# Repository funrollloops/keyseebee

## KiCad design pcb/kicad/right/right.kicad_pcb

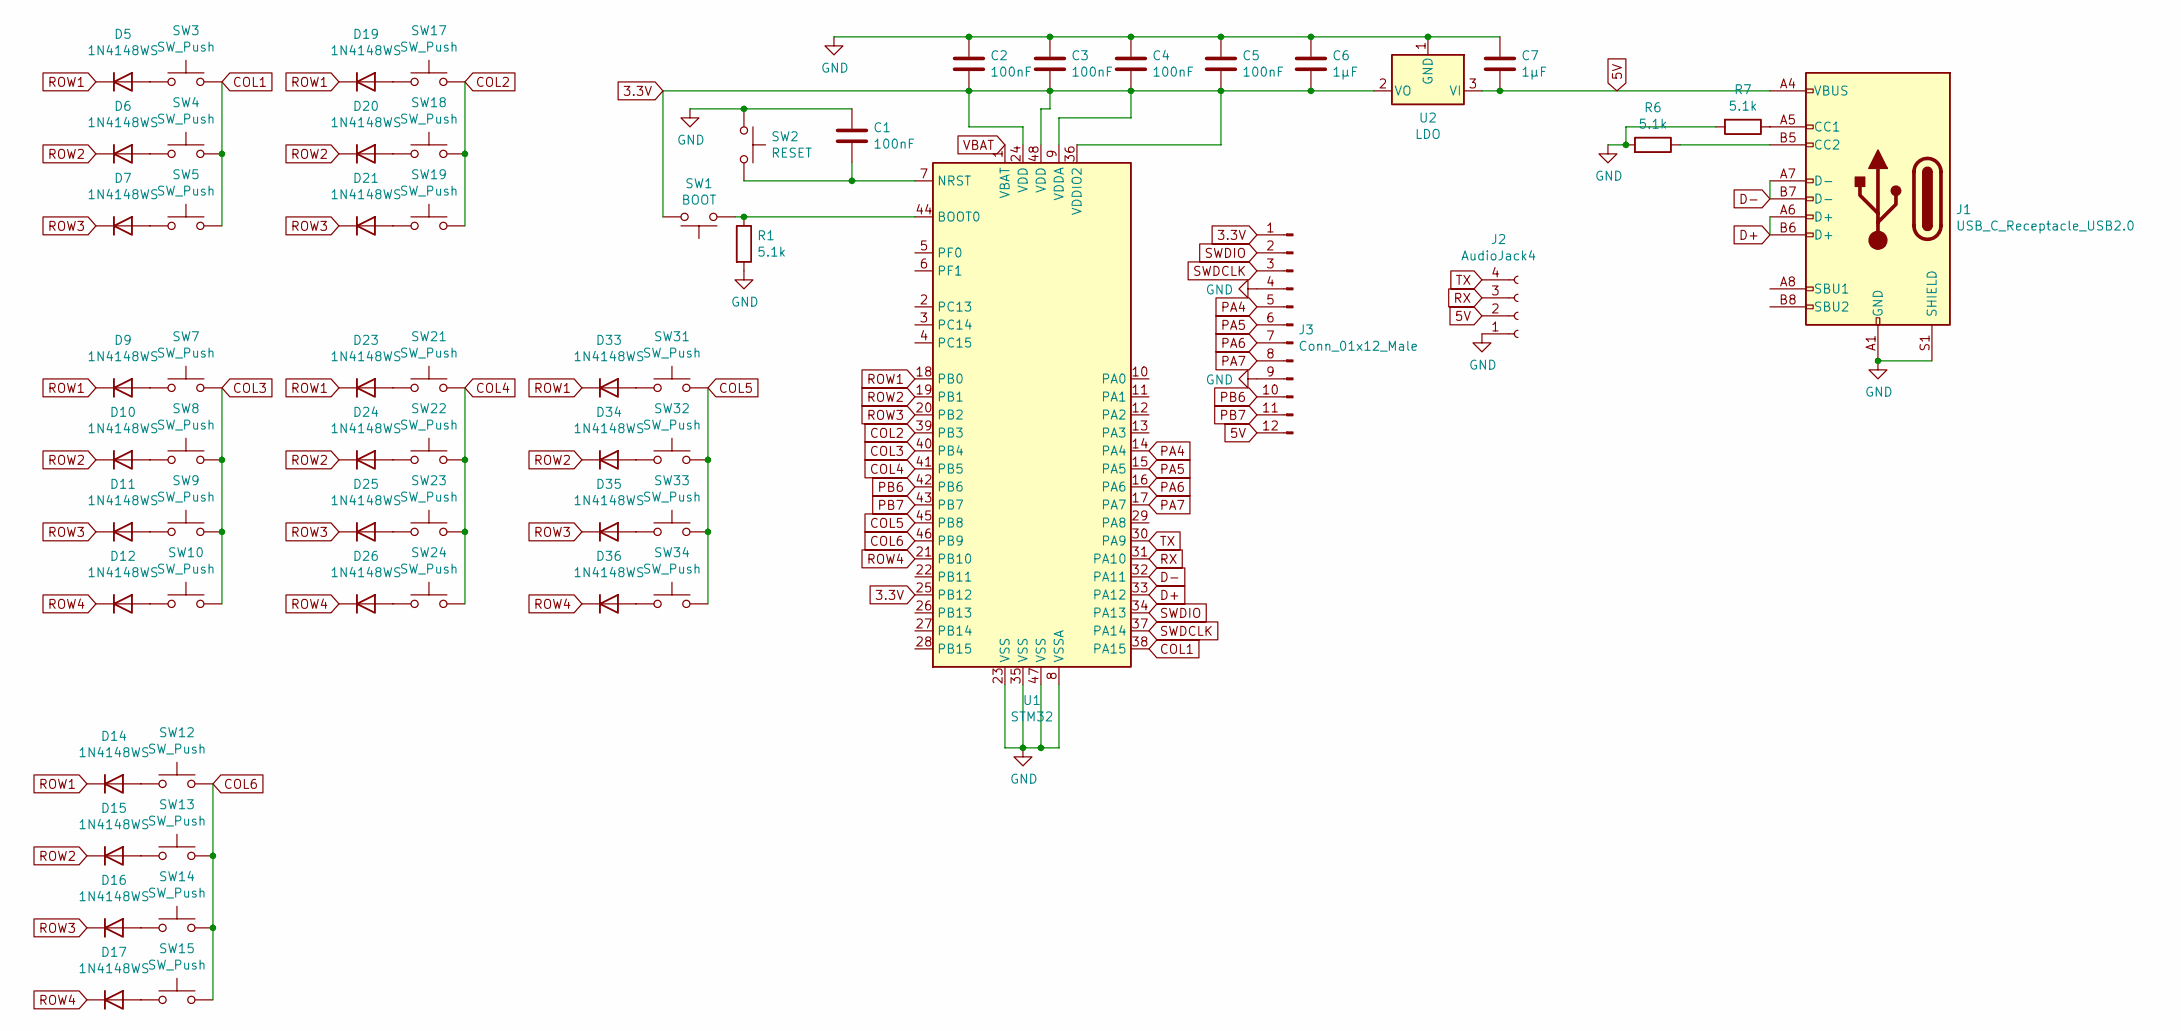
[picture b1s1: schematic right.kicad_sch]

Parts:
C1, C2, C3, C4, C5: 100nF; 0805; JLC C49678
C6, C7: 1µF; 0805; JLC C28323
D5, D6: 1N4148WS; SOD323; JLCPCB Part # C2128
D7, D9, D10, D11, D12, D14, D15, D16, D17, D19, D20, D21, D23, D24, D25, D26, D33, D34, D35, D36: 1N4148WS; SOD323; JLC C2128
J1: USB_C_Receptacle_USB2.0; USB_C_Receptacle_HRO_TYPE-C-31-M-12
J2: AudioJack4; TRRS-PJ-320A-no-Fmask
J3: Conn_01x12_Male; Harwin_M20-89012xx_1x12_P2.54mm_Horizontal
R1, R6, R7: 5.1k; 0805; JLC C27834
SW1: BOOT; SW_SPST_CK_RS282G05A3
SW2: RESET; SW_SPST_CK_RS282G05A3
SW3, SW4, SW5, SW7, SW8, SW9, SW10, SW12, SW13, SW14, SW15, SW17, SW18, SW19, SW21, SW22, SW23, SW24, SW31, SW32, SW33, SW34: SW_Push; CherryMX_Choc_1u
U1: STM32; LQFP-48_7x7mm_P0.5mm; JLCPCB Part # C8734
U2: LDO; SOT-23

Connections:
3.3V: C2.2, C3.2, C4.2, C5.2, C6.2, J3.1, SW1.2, U1.9 (VDDA), U1.24 (VDD), U1.25 (PB12), U1.36 (VDDIO2), U1.48 (VDD), U2.2 (VO)
5V: C7.2, J1.A4 (VBUS), J1.A9 (VBUS), J1.B4 (VBUS), J1.B9 (VBUS), J2.2, J3.12, U2.3 (VI)
COL1: SW3.2, SW4.2, SW5.2, U1.38 (PA15)
COL2: SW17.2, SW18.2, SW19.2, U1.39 (PB3)
COL3: SW7.2, SW8.2, SW9.2, SW10.2, U1.40 (PB4)
COL4: SW21.2, SW22.2, SW23.2, SW24.2, U1.41 (PB5)
COL5: SW31.2, SW32.2, SW33.2, SW34.2, U1.45 (PB8)
COL6: SW12.2, SW13.2, SW14.2, SW15.2, U1.46 (PB9)
D+: J1.A6 (D+), J1.B6 (D+), U1.33 (PA12)
D-: J1.A7 (D-), J1.B7 (D-), U1.32 (PA11)
GND: C1.1, C2.1, C3.1, C4.1, C5.1, C6.1, C7.1, J1.A1 (GND), J1.A12 (GND), J1.B1 (GND), J1.B12 (GND), J1.S1 (SHIELD), J2.1, J3.4, J3.9, R1.2, R6.2, R7.2, SW2.1, U1.8 (VSSA), U1.23 (VSS), U1.35 (VSS), U1.47 (VSS), U2.1 (GND)
unnamed: D5.2 (A), SW3.1
unnamed: D6.2 (A), SW4.1
unnamed: D7.2 (A), SW5.1
unnamed: D9.2 (A), SW7.1
unnamed: D10.2 (A), SW8.1
unnamed: D11.2 (A), SW9.1
unnamed: D12.2 (A), SW10.1
unnamed: D14.2 (A), SW12.1
unnamed: D15.2 (A), SW13.1
unnamed: D16.2 (A), SW14.1
unnamed: D17.2 (A), SW15.1
unnamed: D19.2 (A), SW17.1
unnamed: D20.2 (A), SW18.1
unnamed: D21.2 (A), SW19.1
unnamed: D23.2 (A), SW21.1
unnamed: D24.2 (A), SW22.1
unnamed: D25.2 (A), SW23.1
unnamed: D26.2 (A), SW24.1
unnamed: D33.2 (A), SW31.1
unnamed: D34.2 (A), SW32.1
unnamed: D35.2 (A), SW33.1
unnamed: D36.2 (A), SW34.1
unnamed: J1.A5 (CC1), R7.1
unnamed: J1.B5 (CC2), R6.1
unnamed: R1.1, SW1.1, U1.44 (BOOT0)
unnamed: C1.2, SW2.2, U1.7 (NRST)
PA4: J3.5, U1.14 (PA4)
PA5: J3.6, U1.15 (PA5)
PA6: J3.7, U1.16 (PA6)
PA7: J3.8, U1.17 (PA7)
PB6: J3.10, U1.42 (PB6)
PB7: J3.11, U1.43 (PB7)
ROW1: D5.1 (K), D9.1 (K), D14.1 (K), D19.1 (K), D23.1 (K), D33.1 (K), U1.18 (PB0)
ROW2: D6.1 (K), D10.1 (K), D15.1 (K), D20.1 (K), D24.1 (K), D34.1 (K), U1.19 (PB1)
ROW3: D7.1 (K), D11.1 (K), D16.1 (K), D21.1 (K), D25.1 (K), D35.1 (K), U1.20 (PB2)
ROW4: D12.1 (K), D17.1 (K), D26.1 (K), D36.1 (K), U1.21 (PB10)
RX: J2.3, U1.31 (PA10)
SWDCLK: J3.3, U1.37 (PA14)
SWDIO: J3.2, U1.34 (PA13)
TX: J2.4, U1.30 (PA9)
VBAT: U1.1 (VBAT)

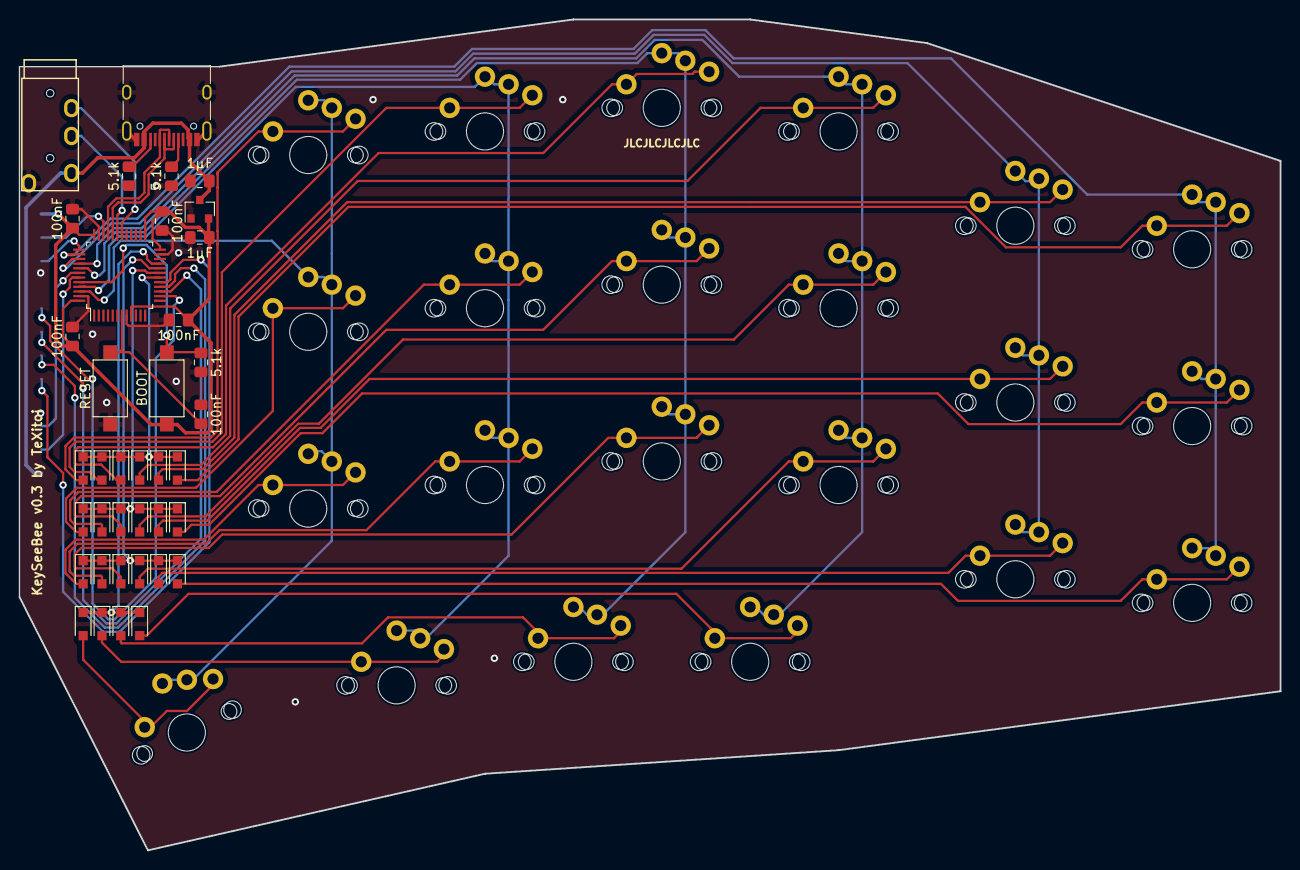
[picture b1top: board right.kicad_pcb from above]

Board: 2 copper layers, 135.9 x 89.5 mm, 61 parts (1 on the bottom side), 51 nets.

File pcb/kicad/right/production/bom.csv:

Designator,Footprint,Quantity,Value,LCSC Part #
"C1, C2, C3, C4, C5",0805,5,100nF,C49678
"C6, C7",0805,2,1µF,C28323
"D10, D11, D12, D14, D15, D16, D17, D19, D20, D21, D23, D24, D25, D26, D33, D34, D35, D36, D5, D6, D7, D9",D_SOD-323_HandSoldering,22,1N4148WS,C2128
"R1, R6, R7",0805,3,5.1k,C27834
U1,LQFP-48_7x7mm_P0.5mm,1,STM32,C8734

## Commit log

2024-03-27 with part nos for production
